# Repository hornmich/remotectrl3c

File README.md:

# remotectrl3c
3 channel remote controller

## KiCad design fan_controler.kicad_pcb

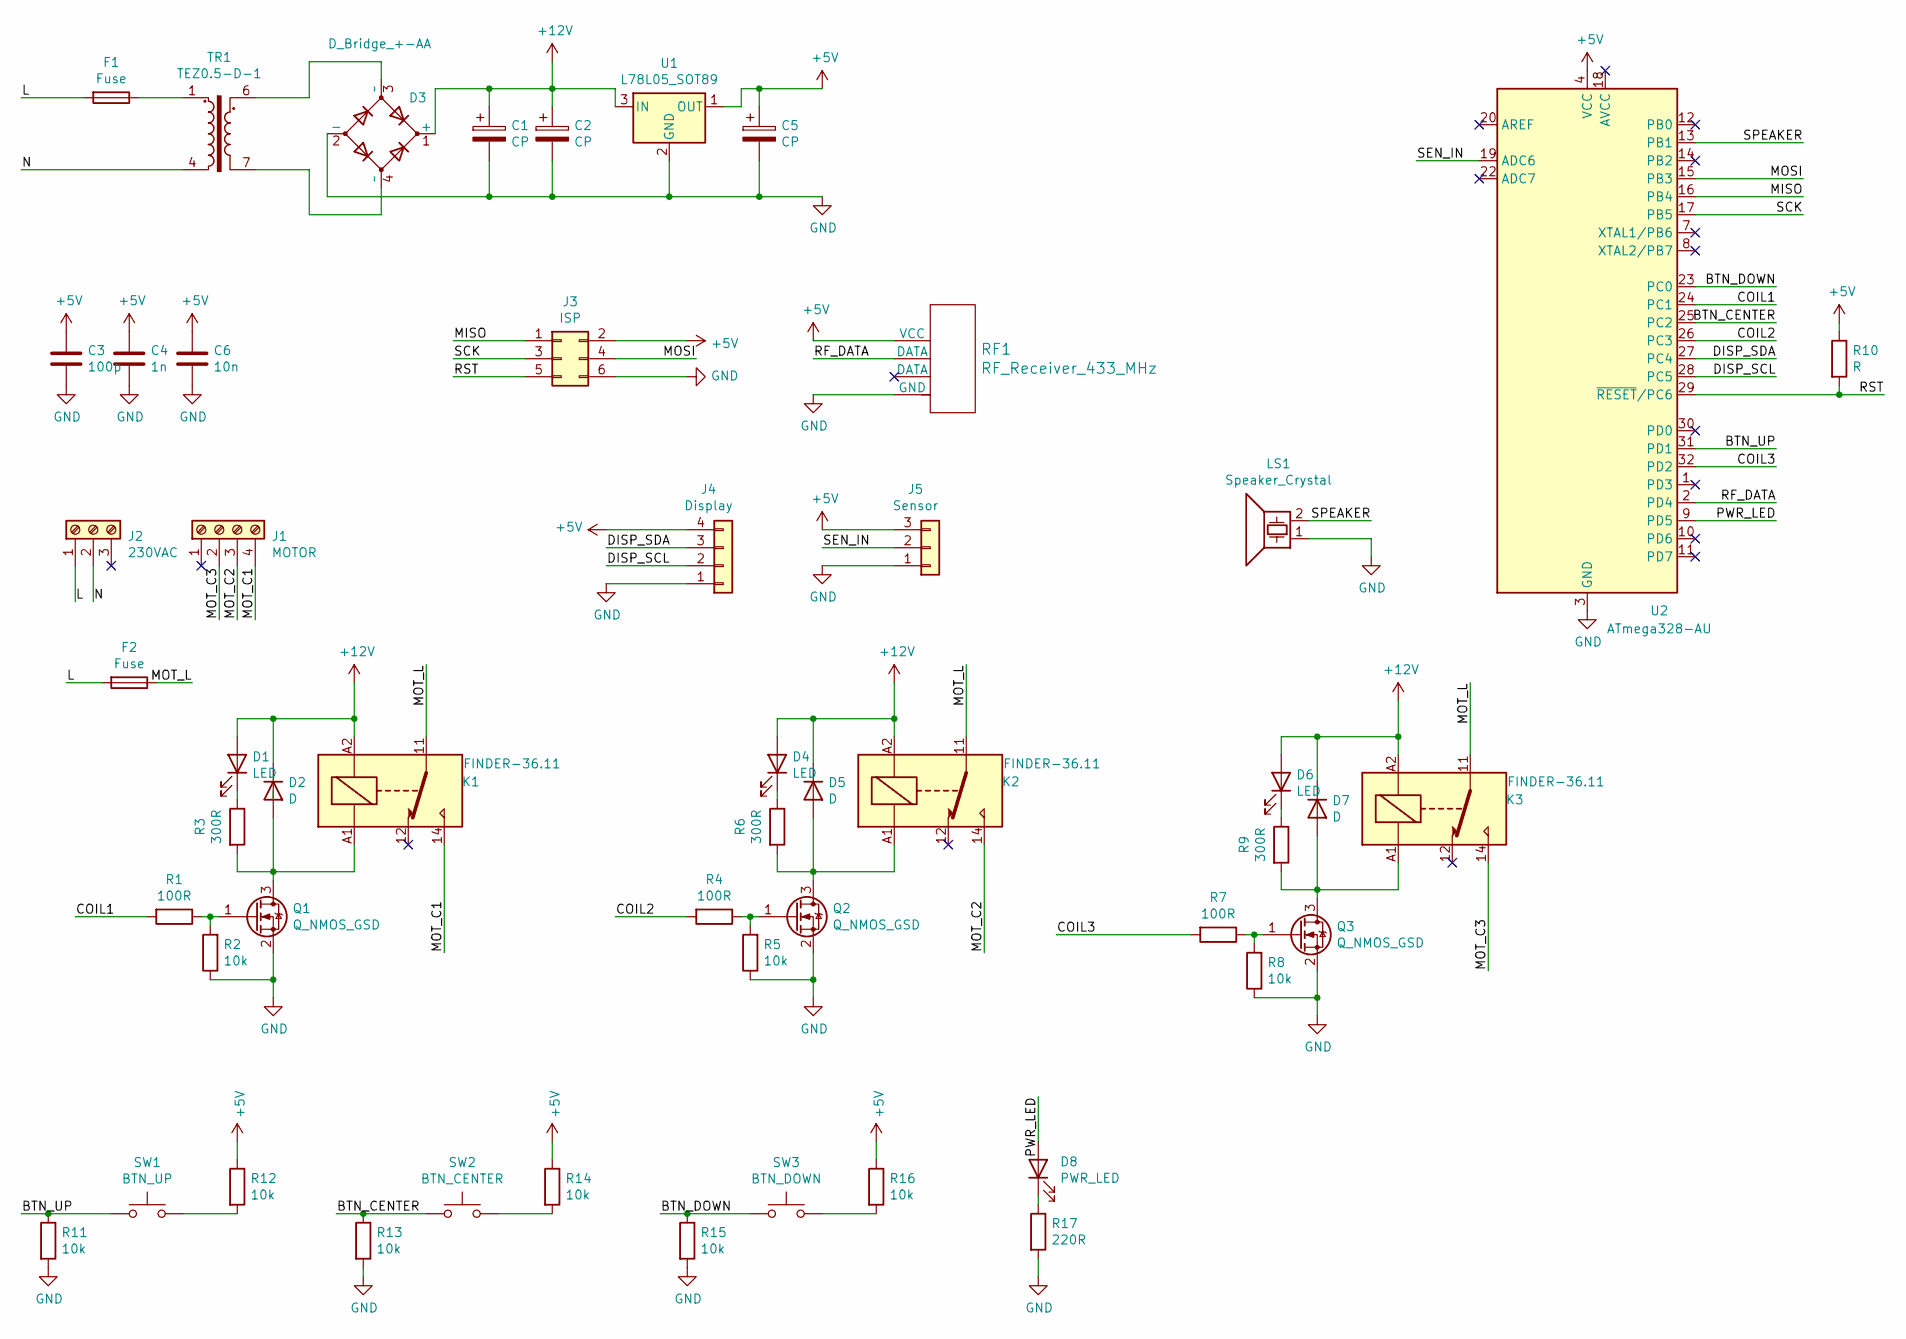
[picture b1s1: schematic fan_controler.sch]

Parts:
C1, C2, C5: CP; CP_Radial_D5.0mm_P2.50mm
C3: 100p; C_0603_1608Metric
C4: 1n; C_0603_1608Metric
C6: 10n; C_0603_1608Metric
D1, D4, D6: LED; D_0603_1608Metric
D2, D5, D7: D; D_0805_2012Metric
D3: D_Bridge_+-AA; Diode_Bridge_Vishay_DFS
D8: PWR_LED; LED_D3.0mm
F1, F2: Fuse; Fuseholder_TR5_Littelfuse_No560_No460
J1: MOTOR; TerminalBlock_Altech_AK300-4_P5.00mm
J2: 230VAC; TerminalBlock_Altech_AK300-3_P5.00mm
J3: ISP; PinHeader_2x03_P1.27mm_Vertical_SMD
J4: Display; PinHeader_1x04_P1.27mm_Vertical
J5: Sensor; PinHeader_1x03_P1.27mm_Vertical
K1, K2, K3: FINDER-36.11; Relay_SPDT_Finder_36.11
LS1: Speaker_Crystal; Buzzer_12x9.5RM7.6
Q1, Q2, Q3: Q_NMOS_GSD; SOT-23
R1, R4, R7: 100R; R_0603_1608Metric
R2, R5, R8, R11, R12, R13, R14, R15, R16: 10k; R_0603_1608Metric
R3, R6, R9: 300R; R_0603_1608Metric
R10: R; R_0603_1608Metric
R17: 220R; R_0603_1608Metric
RF1: RF_Receiver_433_MHz
SW1: BTN_UP; SW_SPST_EVQP0
SW2: BTN_CENTER; SW_SPST_EVQP0
SW3: BTN_DOWN; SW_SPST_EVQP0
TR1: TEZ0.5-D-1; Transformer_Breve_TEZ-22x24
U1: L78L05_SOT89; SOT-89-3
U2: ATmega328-AU; TQFP-32_7x7mm_P0.8mm

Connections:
+5V: C3.1, C4.1, C5.1, C6.1, J3.2, J4.4, J5.3, R10.1, R12.1, R14.1, R16.1, RF1.1 (VCC), U1.1 (OUT), U2.4 (VCC), U2.6 (VCC)
+12V: C1.1, C2.1, D1.2 (A), D2.1 (K), D3.1 (+), D4.2 (A), D5.1 (K), D6.2 (A), D7.1 (K), K1.A2, K2.A2, K3.A2, U1.3 (IN)
/BTN_CENTER: R13.1, SW2.1, U2.25 (PC2)
/BTN_DOWN: R15.1, SW3.1, U2.23 (PC0)
/BTN_UP: R11.1, SW1.1, U2.31 (PD1)
/COIL1: R1.2, U2.24 (PC1)
/COIL2: R4.2, U2.26 (PC3)
/COIL3: R7.2, U2.32 (PD2)
/DISP_SCL: J4.2, U2.28 (PC5)
/DISP_SDA: J4.3, U2.27 (PC4)
/L: F1.2, F2.2, J2.1
/MISO: J3.1, U2.16 (PB4)
/MOSI: J3.4, U2.15 (PB3)
/MOT_C1: J1.4, K1.14
/MOT_C2: J1.3, K2.14
/MOT_C3: J1.2, K3.14
/MOT_L: F2.1, K1.11, K2.11, K3.11
/N: J2.2, TR1.4
/PWR_LED: D8.2 (A), U2.9 (PD5)
/RF_DATA: RF1.2 (DATA), U2.2 (PD4)
/RST: J3.5, R10.2, U2.29 (~RESET~/PC6)
/SCK: J3.3, U2.17 (PB5)
/SEN_IN: J5.2, U2.19 (ADC6)
/SPEAKER: LS1.2, U2.13 (PB1)
GND: C1.2, C2.2, C3.2, C4.2, C5.2, C6.2, D3.2 (-), J3.6, J4.1, J5.1, LS1.1, Q1.2 (S), Q2.2 (S), Q3.2 (S), R2.1, R5.1, R8.1, R11.2, R13.2, R15.2, R17.2, RF1.4 (GND), U1.2 (GND), U2.3 (GND), U2.5 (GND), U2.21 (GND)
unnamed: D1.1 (K), R3.1
unnamed: D2.2 (A), K1.A1, Q1.3 (D), R3.2
unnamed: D3.3 (~~), TR1.6
unnamed: D3.4 (~~), TR1.7
unnamed: D4.1 (K), R6.1
unnamed: D5.2 (A), K2.A1, Q2.3 (D), R6.2
unnamed: D6.1 (K), R9.1
unnamed: D7.2 (A), K3.A1, Q3.3 (D), R9.2
unnamed: D8.1 (K), R17.1
unnamed: F1.1, TR1.1
unnamed: Q1.1 (G), R1.1, R2.2
unnamed: Q2.1 (G), R4.1, R5.2
unnamed: Q3.1 (G), R7.1, R8.2
unnamed: R12.2, SW1.2
unnamed: R14.2, SW2.2
unnamed: R16.2, SW3.2

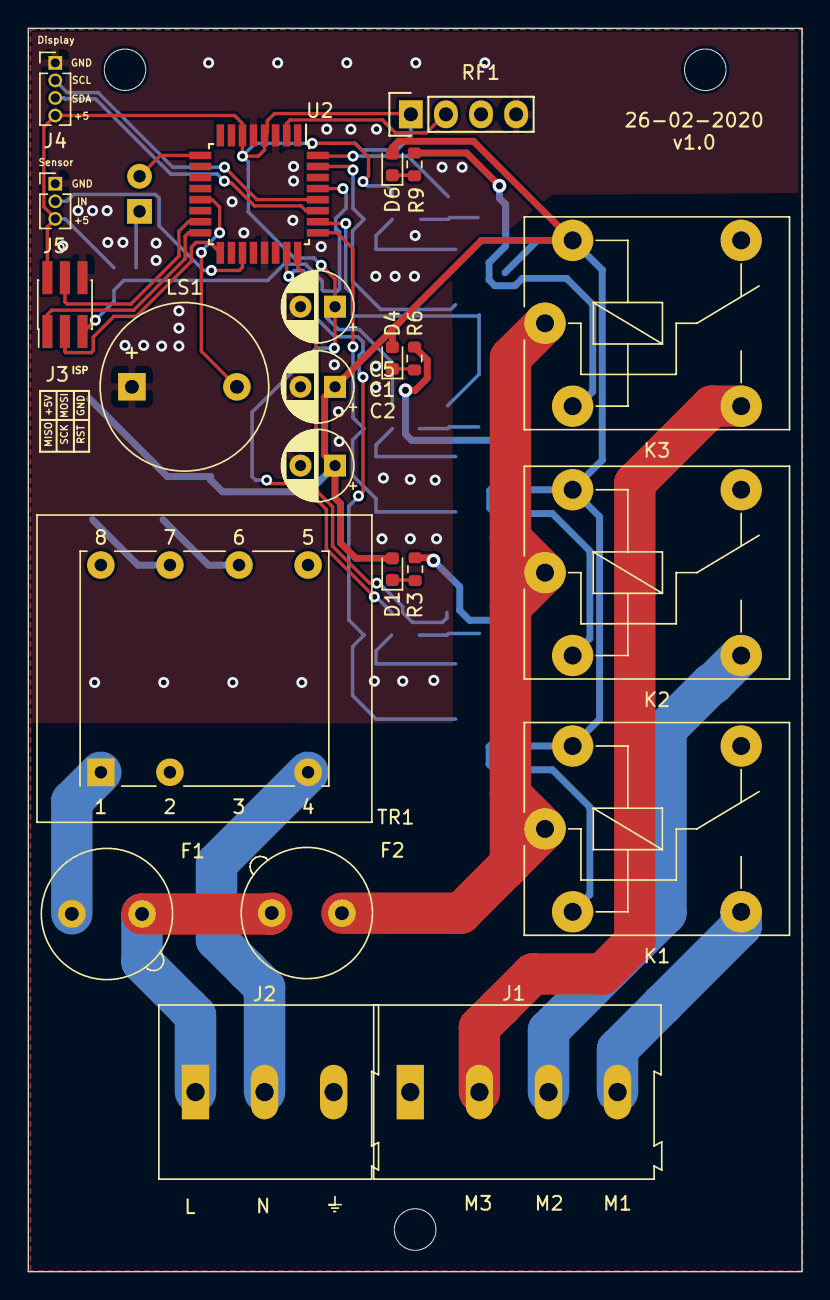
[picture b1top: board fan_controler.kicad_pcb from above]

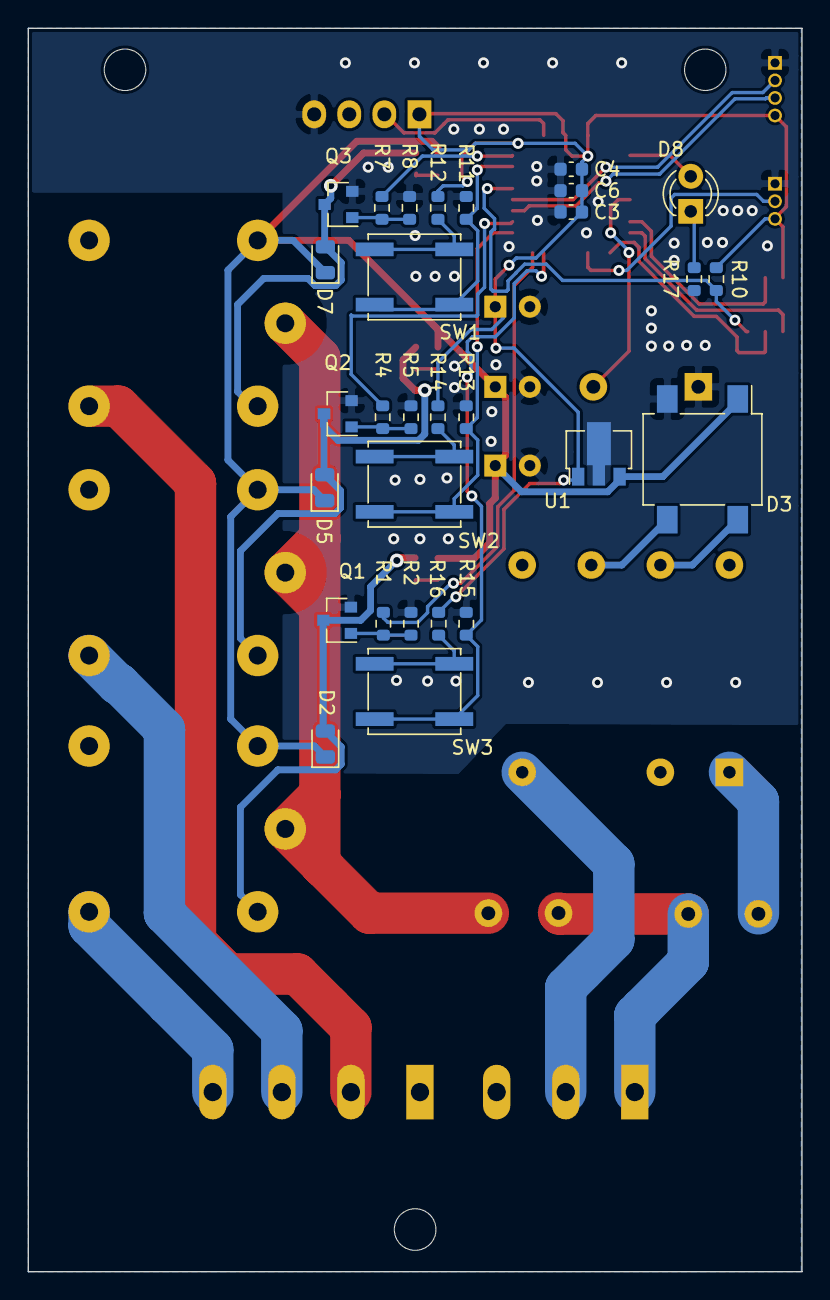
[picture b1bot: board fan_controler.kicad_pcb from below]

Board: 2 copper layers, 56.0 x 90.0 mm, 52 parts (29 on the bottom side), 41 nets.

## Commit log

2021-02-26 Implement HW design
